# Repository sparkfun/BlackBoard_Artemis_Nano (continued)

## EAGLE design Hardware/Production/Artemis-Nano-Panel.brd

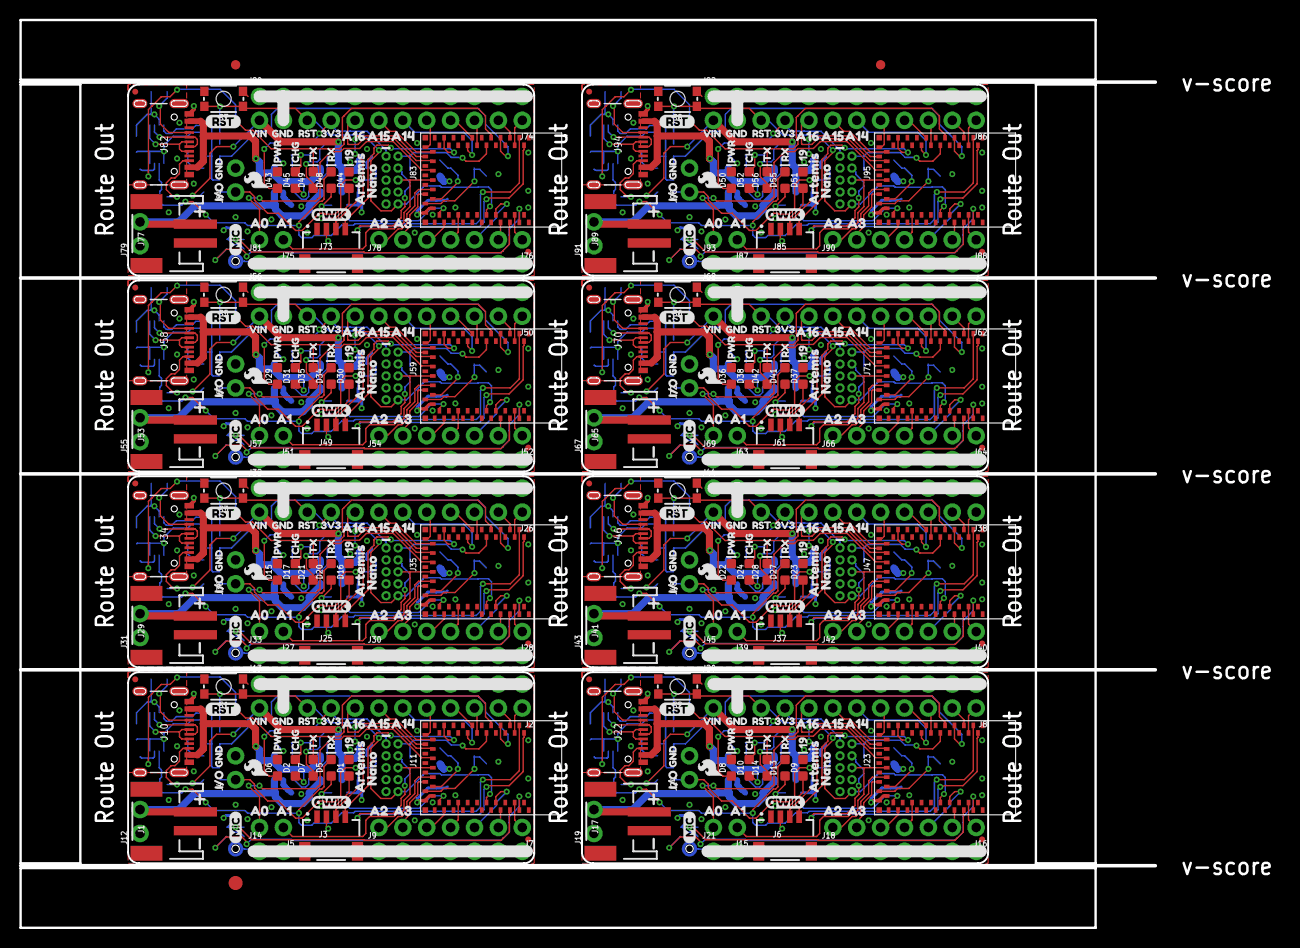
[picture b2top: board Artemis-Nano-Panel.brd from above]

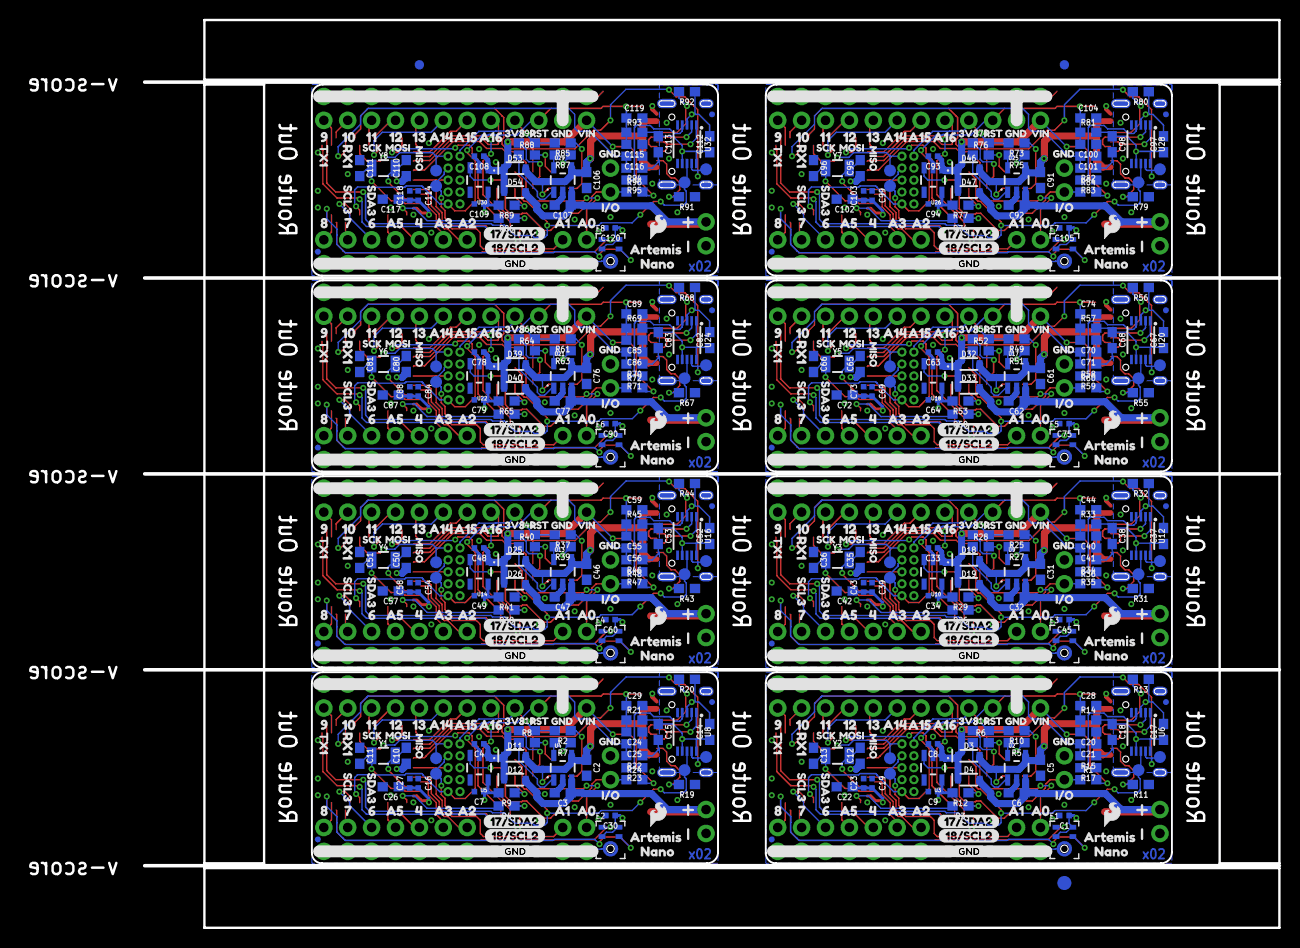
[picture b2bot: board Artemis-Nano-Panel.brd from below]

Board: 4 copper layers, 133.8 x 96.4 mm, 998 parts (627 on the bottom side), 392 nets.

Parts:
C1, C16, C19, C30, C39, C45, C54, C60, C69, C75, C84, C90, C99, C105, C114, C120: 0.1uF; 0402-TIGHT
C2, C3, C5, C6, C31, C32, C46, C47, C61, C62, C76, C77, C91, C92, C106, C107: 4.7uF; 0603
C4, C7, C8, C9, C23, C27, C33, C34, C43, C48, C49, C58, C63, C64, C73, C78, C79, C88, C93, C94, C103, C108, C109, C118: 1.0uF; 0402-TIGHT
C10, C11, C12, C13, C35, C36, C50, C51, C65, C66, C80, C81, C95, C96, C110, C111: 15pF; 0603
C14, C17, C37, C52, C67, C82, C97, C112: 10nF; 0603
C15, C18, C20, C24, C38, C40, C53, C55, C68, C70, C83, C85, C98, C100, C113, C115: 0.1uF; 0603
C21, C25, C41, C56, C71, C86, C101, C116: 2.2uF; 0603
C22, C26, C42, C57, C72, C87, C102, C117: 10uF; 0603
C28, C29, C44, C59, C74, C89, C104, C119: 1nF; 0603
D1, D9, D16, D23, D30, D37, D44, D51: BLUE; LED-0603
D2, D5, D10, D13, D17, D20, D24, D27, D31, D34, D38, D41, D45, D48, D52, D55: Yellow; LED-0603
D3, D4, D11, D12, D18, D19, D25, D26, D32, D33, D39, D40, D46, D47, D53, D54: 1A/23V/620mV; SOD-323
D6, D8, D15, D22, D29, D36, D43, D50: RED; LED-0603
D7, D14, D21, D28, D35, D42, D49, D56: GREEN; LED-0603
E1, E2, E3, E4, E5, E6, E7, E8: SPH0641LM4H; SPH0641LM4H-1_MICROPHONE
E$1, E$2, E$3, E$4: FIDUCIAL-1X2
E$5, E$6: FIDUCIAL-1.5X3
FD1, FD2, FD3, FD4, FD5, FD6, FD7, FD8, FD9, FD10, FD11, FD12, FD13, FD14, FD15, FD16, FD17, FD18, FD19, FD20, FD21, FD22, FD23, FD24, FD25, FD26, FD27, FD28, FD29, FD30, FD31, FD32: FIDUCIALUFIDUCIAL; FIDUCIAL-MICRO
FRAME1, FRAME2, FRAME3, FRAME4, FRAME5, FRAME6, FRAME7, FRAME8: FRAME-LETTERNO_PACKAGE; DUMMY
J1, J17, J29, J41, J53, J65, J77, J89: JST-2-SMD
J2, J8, J13, J20, J26, J32, J38, J44, J50, J56, J62, J68, J74, J80, J86, J92: 1X12_NO_SILK
J3, J6, J25, J37, J49, J61, J73, J85: JST04_1MM_RA
J4, J5, J12, J14, J15, J19, J21, J24, J27, J31, J33, J36, J39, J43, J45, J48, J51, J55, J57, J60, J63, J67, J69, J72, J75, J79, J81, J84, J87, J91, J93, J96: 1X02_NO_SILK
J7, J9, J16, J18, J28, J30, J40, J42, J52, J54, J64, J66, J76, J78, J88, J90: 1X07_NO_SILK
J10, J22, J34, J46, J58, J70, J82, J94: USB-C; USB-C-16P
J11, J23, J35, J47, J59, J71, J83, J95: CORTEX_DEBUG; 2X5-PTH-1.27MM-NO_SILK
LOGO1, LOGO2, LOGO3, LOGO4, LOGO5, LOGO6, LOGO7, LOGO8, LOGO9, LOGO10, LOGO11, LOGO12, LOGO13, LOGO14, LOGO15, LOGO16: SFE_LOGO_FLAME.1_INCH; SFE_LOGO_FLAME_.1
R1, R15, R22, R24, R34, R36, R46, R48, R58, R60, R70, R72, R82, R84, R94, R96: 10k; 0603
R2, R3, R4, R6, R8, R10, R25, R26, R28, R37, R38, R40, R49, R50, R52, R61, R62, R64, R73, R74, R76, R85, R86, R88: 1k; 0603
R5, R7, R27, R39, R51, R63, R75, R87: 2.0k; 0603
R9, R12, R16, R18, R29, R30, R41, R42, R53, R54, R65, R66, R77, R78, R89, R90: 4.7k; 0603
R11, R13, R19, R20, R31, R32, R43, R44, R55, R56, R67, R68, R79, R80, R91, R92: 5.1k; 0603
R14, R17, R21, R23, R33, R35, R45, R47, R57, R59, R69, R71, R81, R83, R93, R95: 100k; 0603
S1, S2, S3, S4, S5, S6, S7, S8: RESET; TACTILE_SWITCH_SMD_4.6X2.8MM
TP1, TP2, TP7, TP8, TP11, TP12, TP15, TP16, TP19, TP20, TP23, TP24, TP27, TP28, TP31, TP32: PAD.03X.05
TP3, TP4, TP5, TP6, TP9, TP10, TP13, TP14, TP17, TP18, TP21, TP22, TP25, TP26, TP29, TP30: TEST-POINT3X5; PAD.03X.05
U1, U7, U11, U15, U19, U23, U27, U31: ARTEMIS_MODULESMD; ARTEMIS_FP
U2, U4, U9, U13, U17, U21, U25, U29: MCP73831; SOT23-5
U3, U5, U10, U14, U18, U22, U26, U30: 3.3V; SOT23-5
U6, U8, U12, U16, U20, U24, U28, U32: CH340E_MSOP10; MSOP10
U$1, U$49, U$65, U$72, U$127, U$134, U$187, U$194, U$247, U$254, U$307, U$314, U$367, U$374, U$427, U$434: 3V316
U$2, U$82, U$144, U$204, U$264, U$324, U$384, U$444: ____GND____2
U$3, U$38, U$64, U$70, U$126, U$132, U$186, U$192, U$246, U$252, U$306, U$312, U$366, U$372, U$426, U$432: RST19
U$4, U$23, U$117, U$119, U$177, U$179, U$237, U$239, U$297, U$299, U$357, U$359, U$417, U$419, U$477, U$479: I#O3
U$5, U$44, U$121, U$181, U$241, U$301, U$361, U$421: CHG26
U$6, U$58, U$122, U$182, U$242, U$302, U$362, U$422: PWR27
U$7, U$29, U$33, U$43, U$62, U$69, U$118, U$120, U$124, U$131, U$178, U$180, U$184, U$191, U$238, U$240, U$244, U$251, U$298, U$300, U$304, U$311, U$358, U$360, U$364, U$371, U$418, U$420, U$424, U$431, U$478, U$480: GND17
U$8, U$61, U$123, U$183, U$243, U$303, U$363, U$423: QWIIC#LOGO#JPG
U$9, U$20, U$84, U$108, U$146, U$168, U$206, U$228, U$266, U$288, U$326, U$348, U$386, U$408, U$446, U$468: A00
U$10, U$105, U$165, U$225, U$285, U$345, U$405, U$465: A57
U$11, U$102, U$162, U$222, U$282, U$342, U$402, U$462: SCL30
U$12, U$54, U$99, U$110, U$159, U$170, U$219, U$230, U$279, U$290, U$339, U$350, U$399, U$410, U$459, U$470: A145
U$13, U$22, U$73, U$79, U$135, U$141, U$195, U$201, U$255, U$261, U$315, U$321, U$375, U$381, U$435, U$441: ARTEMIS6
U$14, U$75, U$137, U$197, U$257, U$317, U$377, U$437: MISO5
U$15, U$74, U$136, U$196, U$256, U$316, U$376, U$436: MIC0
U$16, U$76, U$138, U$198, U$258, U$318, U$378, U$438: MOSI4
U$17, U$24, U$77, U$80, U$139, U$142, U$199, U$202, U$259, U$262, U$319, U$322, U$379, U$382, U$439, U$442: NANO7
U$18, U$78, U$140, U$200, U$260, U$320, U$380, U$440: SCK3
U$19, U$42, U$93, U$106, U$153, U$166, U$213, U$226, U$273, U$286, U$333, U$346, U$393, U$406, U$453, U$466: A32
U$21, U$41, U$92, U$107, U$152, U$167, U$212, U$227, U$272, U$287, U$332, U$347, U$392, U$407, U$452, U$467: A21
U$25, U$83, U$145, U$205, U$265, U$325, U$385, U$445: PRODUCTION_INSTRUCTIONS
U$26, U$116, U$176, U$236, U$296, U$356, U$416, U$476: 191
U$27, U$39, U$63, U$71, U$125, U$133, U$185, U$193, U$245, U$253, U$305, U$313, U$365, U$373, U$425, U$433: VIN19
U$28, U$55, U$100, U$111, U$160, U$171, U$220, U$231, U$280, U$291, U$340, U$351, U$400, U$411, U$460, U$471: A156
U$30, U$81, U$143, U$203, U$263, U$323, U$383, U$443: GND2
U$31, U$103, U$163, U$223, U$283, U$343, U$403, U$463: SDA31
U$32, U$87, U$147, U$207, U$267, U$327, U$387, U$447: 46
U$34, U$40, U$91, U$109, U$151, U$169, U$211, U$229, U$271, U$289, U$331, U$349, U$391, U$409, U$451, U$469: A10
U$35, U$88, U$148, U$208, U$268, U$328, U$388, U$448: 68
U$36, U$89, U$149, U$209, U$269, U$329, U$389, U$449: 79
U$37, U$90, U$150, U$210, U$270, U$330, U$390, U$450: 810
U$45, U$94, U$154, U$214, U$274, U$334, U$394, U$454: 90
U$46, U$95, U$155, U$215, U$275, U$335, U$395, U$455: 101
U$47, U$96, U$156, U$216, U$276, U$336, U$396, U$456: 112
U$48, U$56, U$101, U$112, U$161, U$172, U$221, U$232, U$281, U$292, U$341, U$352, U$401, U$412, U$461, U$472: A167
U$50, U$113, U$173, U$233, U$293, U$353, U$413, U$473: RX10
U$51, U$66, U$128, U$188, U$248, U$308, U$368, U$428: RST1
U$52, U$97, U$157, U$217, U$277, U$337, U$397, U$457: 123
U$53, U$98, U$158, U$218, U$278, U$338, U$398, U$458: 134
U$57, U$114, U$174, U$234, U$294, U$354, U$414, U$474: 17#SDA21
U$59, U$104, U$164, U$224, U$284, U$344, U$404, U$464: TX12
U$60, U$115, U$175, U$235, U$295, U$355, U$415, U$475: 18#SCL20
U$67, U$85, U$129, U$189, U$249, U$309, U$369, U$429: RX23
U$68, U$86, U$130, U$190, U$250, U$310, U$370, U$430: TX22
Y1, Y2, Y3, Y4, Y5, Y6, Y7, Y8: 32.768kHz; CRYSTAL-SMD-3.2X1.5MM

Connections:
1: J16.1, U7.D38
2: J8.2, U7.D40
3: J28.1, U11.D38
3.3V: C1.1, C9.1, C17.1, C18.1, C19.2, C22.1, C23.1, E1.2, E1.5, J2.9, J3.2, J11.1, R10.2, R12.2, R14.2, R16.2, U1.VDD@36, U1.VDD@37, U3.5, U6.7, U6.10
3.3V1: C7.1, C14.1, C15.1, C16.2, C26.1, C27.1, C30.1, E2.2, E2.5, J6.2, J8.9, J23.1, R2.2, R9.2, R18.2, R21.2, U5.5, U7.VDD@36, U7.VDD@37, U8.7, U8.10
3.3V2: C34.1, C37.1, C38.1, C39.2, C42.1, C43.1, C45.1, E3.2, E3.5, J25.2, J26.9, J35.1, R25.2, R29.2, R30.2, R33.2, U10.5, U11.VDD@36, U11.VDD@37, U12.7, U12.10
3.3V3: C49.1, C52.1, C53.1, C54.2, C57.1, C58.1, C60.1, E4.2, E4.5, J37.2, J38.9, J47.1, R37.2, R41.2, R42.2, R45.2, U14.5, U15.VDD@36, U15.VDD@37, U16.7, U16.10
3.3V4: C64.1, C67.1, C68.1, C69.2, C72.1, C73.1, C75.1, E5.2, E5.5, J49.2, J50.9, J59.1, R49.2, R53.2, R54.2, R57.2, U18.5, U19.VDD@36, U19.VDD@37, U20.7, U20.10
3.3V5: C79.1, C82.1, C83.1, C84.2, C87.1, C88.1, C90.1, E6.2, E6.5, J61.2, J62.9, J71.1, R61.2, R65.2, R66.2, R69.2, U22.5, U23.VDD@36, U23.VDD@37, U24.7, U24.10
3.3V6: C94.1, C97.1, C98.1, C99.2, C102.1, C103.1, C105.1, E7.2, E7.5, J73.2, J74.9, J83.1, R73.2, R77.2, R78.2, R81.2, U26.5, U27.VDD@36, U27.VDD@37, U28.7, U28.10
3.3V7: C109.1, C112.1, C113.1, C114.2, C117.1, C118.1, C120.1, E8.2, E8.5, J85.2, J86.9, J95.1, R85.2, R89.2, R90.2, R93.2, U30.5, U31.VDD@36, U31.VDD@37, U32.7, U32.10
4: J26.2, U11.D40
5: J40.1, U15.D38
6: J38.2, U15.D40
7: J52.1, U19.D38
8: J7.1, U1.D38
9: J50.2, U19.D40
10: J2.2, U1.D40
11: J64.1, U23.D38
12: J62.2, U23.D40
13: J76.1, U27.D38
14: J74.2, U27.D40
15: J88.1, U31.D38
16: J86.2, U31.D40
!RESET: C20.2, C28.1, J2.10, J11.10, R14.1, S1.3, S1.4, U1.~RST
!RESET1: C24.2, C29.1, J8.10, J23.10, R21.1, S2.3, S2.4, U7.~RST
!RESET2: C40.2, C44.1, J26.10, J35.10, R33.1, S3.3, S3.4, U11.~RST
!RESET3: C55.2, C59.1, J38.10, J47.10, R45.1, S4.3, S4.4, U15.~RST
!RESET4: C70.2, C74.1, J50.10, J59.10, R57.1, S5.3, S5.4, U19.~RST
!RESET5: C85.2, C89.1, J62.10, J71.10, R69.1, S6.3, S6.4, U23.~RST
!RESET6: C100.2, C104.1, J74.10, J83.10, R81.1, S7.3, S7.4, U27.~RST
!RESET7: C115.2, C119.1, J86.10, J95.10, R93.1, S8.3, S8.4, U31.~RST
!RTS: C20.1, C21.1, R17.2, U6.4
!RTS1: C24.1, C25.1, R23.2, U8.4
!RTS2: C40.1, C41.1, R35.2, U12.4
!RTS3: C55.1, C56.1, R47.2, U16.4
!RTS4: C70.1, C71.1, R59.2, U20.4
!RTS5: C85.1, C86.1, R71.2, U24.4
!RTS6: C100.1, C101.1, R83.2, U28.4
!RTS7: C115.1, C116.1, R95.2, U32.4
BOOT: C21.2, R15.2, U1.BOOT
BOOT1: C25.2, R22.2, U7.BOOT
BOOT2: C41.2, R34.2, U11.BOOT
BOOT3: C56.2, R46.2, U15.BOOT
BOOT4: C71.2, R58.2, U19.BOOT
BOOT5: C86.2, R70.2, U23.BOOT
BOOT6: C101.2, R82.2, U27.BOOT
BOOT7: C116.2, R94.2, U31.BOOT
CC1: J10.A5, R13.2
CC2: J10.B5, R11.2
CC3: J22.B5, R19.2
CC4: J22.A5, R20.2
CC5: J34.B5, R31.2
CC6: J34.A5, R32.2
CC7: J46.B5, R43.2
CC8: J46.A5, R44.2
CC9: J58.B5, R55.2
CC10: J58.A5, R56.2
CC11: J70.B5, R67.2
CC12: J70.A5, R68.2
CC13: J82.B5, R79.2
CC14: J82.A5, R80.2
CC15: J94.B5, R91.2
CC16: J94.A5, R92.2
D+1: J10.A6, J10.B6, U6.1
D+2: J22.A6, J22.B6, U8.1
D+3: J34.A6, J34.B6, U12.1
D+4: J46.A6, J46.B6, U16.1
D+5: J58.A6, J58.B6, U20.1
D+6: J70.A6, J70.B6, U24.1
D+7: J82.A6, J82.B6, U28.1
D+8: J94.A6, J94.B6, U32.1
D-1: J10.A7, J10.B7, U6.2
D-2: J22.A7, J22.B7, U8.2
D-3: J34.A7, J34.B7, U12.2
D-4: J46.A7, J46.B7, U16.2
D-5: J58.A7, J58.B7, U20.2
D-6: J70.A7, J70.B7, U24.2
D-7: J82.A7, J82.B7, U28.2
D-8: J94.A7, J94.B7, U32.2
GND: C1.2, C5.2, C6.2, C8.2, C9.2, C12.1, C13.1, C17.2, C18.2, C19.1, C22.2, C23.2, C28.2, D1.C, D6.C, E1.3, E1.6, E1.7, E1.8, J1.1, J2.11, J3.1, J4.2, J9.1, J9.2, J9.3, J9.4, J9.5, J9.6, J9.7, J10.GND, J10.GND2, J11.3, J11.5, J11.9, J12.1, J13.1, J13.2, J13.3, J13.4, J13.5, J13.6, J13.7, J13.8, J13.9, J13.10, J13.11, J13.12, J14.1, J14.2, R5.1, R11.1, R13.1, R15.1, R17.1, S1.1, S1.2, U1.GND@1, U1.GND@22, U1.GND@38, U1.GND@39, U1.GND@47, U1.GND@59, U2.2, U3.2, U6.3
GND1: C2.2, C3.2, C4.2, C7.2, C10.1, C11.1, C14.2, C15.2, C16.1, C26.2, C27.2, C29.2, C30.2, D8.C, D9.C, E2.3, E2.6, E2.7, E2.8, J6.1, J8.11, J17.1, J18.1, J18.2, J18.3, J18.4, J18.5, J18.6, J18.7, J19.1, J20.1, J20.2, J20.3, J20.4, J20.5, J20.6, J20.7, J20.8, J20.9, J20.10, J20.11, J20.12, J21.1, J21.2, J22.GND, J22.GND2, J23.3, J23.5, J23.9, J24.2, R7.1, R19.1, R20.1, R22.1, R23.1, S2.1, S2.2, U4.2, U5.2, U7.GND@1, U7.GND@22, U7.GND@38, U7.GND@39, U7.GND@47, U7.GND@59, U8.3
GND2: C31.2, C32.2, C33.2, C34.2, C35.1, C36.1, C37.2, C38.2, C39.1, C42.2, C43.2, C44.2, C45.2, D15.C, D16.C, E3.3, E3.6, E3.7, E3.8, J25.1, J26.11, J29.1, J30.1, J30.2, J30.3, J30.4, J30.5, J30.6, J30.7, J31.1, J32.1, J32.2, J32.3, J32.4, J32.5, J32.6, J32.7, J32.8, J32.9, J32.10, J32.11, J32.12, J33.1, J33.2, J34.GND, J34.GND2, J35.3, J35.5, J35.9, J36.2, R27.1, R31.1, R32.1, R34.1, R35.1, S3.1, S3.2, U9.2, U10.2, U11.GND@1, U11.GND@22, U11.GND@38, U11.GND@39, U11.GND@47, U11.GND@59, U12.3
GND3: C46.2, C47.2, C48.2, C49.2, C50.1, C51.1, C52.2, C53.2, C54.1, C57.2, C58.2, C59.2, C60.2, D22.C, D23.C, E4.3, E4.6, E4.7, E4.8, J37.1, J38.11, J41.1, J42.1, J42.2, J42.3, J42.4, J42.5, J42.6, J42.7, J43.1, J44.1, J44.2, J44.3, J44.4, J44.5, J44.6, J44.7, J44.8, J44.9, J44.10, J44.11, J44.12, J45.1, J45.2, J46.GND, J46.GND2, J47.3, J47.5, J47.9, J48.2, R39.1, R43.1, R44.1, R46.1, R47.1, S4.1, S4.2, U13.2, U14.2, U15.GND@1, U15.GND@22, U15.GND@38, U15.GND@39, U15.GND@47, U15.GND@59, U16.3
GND4: C61.2, C62.2, C63.2, C64.2, C65.1, C66.1, C67.2, C68.2, C69.1, C72.2, C73.2, C74.2, C75.2, D29.C, D30.C, E5.3, E5.6, E5.7, E5.8, J49.1, J50.11, J53.1, J54.1, J54.2, J54.3, J54.4, J54.5, J54.6, J54.7, J55.1, J56.1, J56.2, J56.3, J56.4, J56.5, J56.6, J56.7, J56.8, J56.9, J56.10, J56.11, J56.12, J57.1, J57.2, J58.GND, J58.GND2, J59.3, J59.5, J59.9, J60.2, R51.1, R55.1, R56.1, R58.1, R59.1, S5.1, S5.2, U17.2, U18.2, U19.GND@1, U19.GND@22, U19.GND@38, U19.GND@39, U19.GND@47, U19.GND@59, U20.3
GND5: C76.2, C77.2, C78.2, C79.2, C80.1, C81.1, C82.2, C83.2, C84.1, C87.2, C88.2, C89.2, C90.2, D36.C, D37.C, E6.3, E6.6, E6.7, E6.8, J61.1, J62.11, J65.1, J66.1, J66.2, J66.3, J66.4, J66.5, J66.6, J66.7, J67.1, J68.1, J68.2, J68.3, J68.4, J68.5, J68.6, J68.7, J68.8, J68.9, J68.10, J68.11, J68.12, J69.1, J69.2, J70.GND, J70.GND2, J71.3, J71.5, J71.9, J72.2, R63.1, R67.1, R68.1, R70.1, R71.1, S6.1, S6.2, U21.2, U22.2, U23.GND@1, U23.GND@22, U23.GND@38, U23.GND@39, U23.GND@47, U23.GND@59, U24.3
GND6: C91.2, C92.2, C93.2, C94.2, C95.1, C96.1, C97.2, C98.2, C99.1, C102.2, C103.2, C104.2, C105.2, D43.C, D44.C, E7.3, E7.6, E7.7, E7.8, J73.1, J74.11, J77.1, J78.1, J78.2, J78.3, J78.4, J78.5, J78.6, J78.7, J79.1, J80.1, J80.2, J80.3, J80.4, J80.5, J80.6, J80.7, J80.8, J80.9, J80.10, J80.11, J80.12, J81.1, J81.2, J82.GND, J82.GND2, J83.3, J83.5, J83.9, J84.2, R75.1, R79.1, R80.1, R82.1, R83.1, S7.1, S7.2, U25.2, U26.2, U27.GND@1, U27.GND@22, U27.GND@38, U27.GND@39, U27.GND@47, U27.GND@59, U28.3
GND7: C106.2, C107.2, C108.2, C109.2, C110.1, C111.1, C112.2, C113.2, C114.1, C117.2, C118.2, C119.2, C120.2, D50.C, D51.C, E8.3, E8.6, E8.7, E8.8, J85.1, J86.11, J89.1, J90.1, J90.2, J90.3, J90.4, J90.5, J90.6, J90.7, J91.1, J92.1, J92.2, J92.3, J92.4, J92.5, J92.6, J92.7, J92.8, J92.9, J92.10, J92.11, J92.12, J93.1, J93.2, J94.GND, J94.GND2, J95.3, J95.5, J95.9, J96.2, R87.1, R91.1, R92.1, R94.1, R95.1, S8.1, S8.2, U29.2, U30.2, U31.GND@1, U31.GND@22, U31.GND@38, U31.GND@39, U31.GND@47, U31.GND@59, U32.3
unnamed: R5.2, U2.5
unnamed: C12.2, U1.XO, Y2.P$2
unnamed: D2.C, R6.2
unnamed: R6.1, U2.1
unnamed: D7.A, R16.1
unnamed: D8.A, R2.1
unnamed: D1.A, R3.1
unnamed: C13.2, U1.XI, Y2.P$1
unnamed: D5.A, R12.1
unnamed: D6.A, R10.1
unnamed: D9.A, R4.1
unnamed: R7.2, U4.5
unnamed: D10.C, R8.2
unnamed: R8.1, U4.1
unnamed: C10.2, U7.XO, Y1.P$2
unnamed: C11.2, U7.XI, Y1.P$1
unnamed: D14.A, R18.1
unnamed: D13.A, R9.1
unnamed: D15.A, R25.1
unnamed: D16.A, R26.1
unnamed: R27.2, U9.5
unnamed: D17.C, R28.2
unnamed: R28.1, U9.1
unnamed: C35.2, U11.XO, Y3.P$2
unnamed: C36.2, U11.XI, Y3.P$1
unnamed: D21.A, R30.1
unnamed: D20.A, R29.1
unnamed: D22.A, R37.1
unnamed: D23.A, R38.1
unnamed: R39.2, U13.5
unnamed: D24.C, R40.2
unnamed: R40.1, U13.1
unnamed: C50.2, U15.XO, Y4.P$2
unnamed: C51.2, U15.XI, Y4.P$1
unnamed: D28.A, R42.1
unnamed: D27.A, R41.1
unnamed: D29.A, R49.1
unnamed: D30.A, R50.1
unnamed: R51.2, U17.5
unnamed: D31.C, R52.2
unnamed: R52.1, U17.1
unnamed: C65.2, U19.XO, Y5.P$2
unnamed: C66.2, U19.XI, Y5.P$1
unnamed: D35.A, R54.1
unnamed: D34.A, R53.1
unnamed: D36.A, R61.1
unnamed: D37.A, R62.1
unnamed: R63.2, U21.5
unnamed: D38.C, R64.2
unnamed: R64.1, U21.1
unnamed: C80.2, U23.XO, Y6.P$2
unnamed: C81.2, U23.XI, Y6.P$1
unnamed: D42.A, R66.1
unnamed: D41.A, R65.1
unnamed: D43.A, R73.1
unnamed: D44.A, R74.1
unnamed: R75.2, U25.5
unnamed: D45.C, R76.2
unnamed: R76.1, U25.1
unnamed: C95.2, U27.XO, Y7.P$2
unnamed: C96.2, U27.XI, Y7.P$1
unnamed: D49.A, R78.1
unnamed: D48.A, R77.1
unnamed: D50.A, R85.1
unnamed: D51.A, R86.1
unnamed: R87.2, U29.5
unnamed: D52.C, R88.2
unnamed: R88.1, U29.1
unnamed: C110.2, U31.XO, Y8.P$2
unnamed: C111.2, U31.XI, Y8.P$1
unnamed: D56.A, R90.1
unnamed: D55.A, R89.1
PDMCLK: E1.4, U1.~D37
PDMCLK1: E2.4, U7.~D37
PDMCLK2: E3.4, U11.~D37
PDMCLK3: E4.4, U15.~D37
PDMCLK4: E5.4, U19.~D37
PDMCLK5: E6.4, U23.~D37
PDMCLK6: E7.4, U27.~D37
PDMCLK7: E8.4, U31.~D37
PDMDATA: E1.1, U1.D36
PDMDATA1: E2.1, U7.D36
PDMDATA2: E3.1, U11.D36
PDMDATA3: E4.1, U15.D36
PDMDATA4: E5.1, U19.D36
PDMDATA5: E6.1, U23.D36
PDMDATA6: E7.1, U27.D36
PDMDATA7: E8.1, U31.D36
RXI-0: D5.C, TP5.P$1, U1.RXI-0, U6.8
RXI-1: D13.C, TP3.P$1, U7.RXI-0, U8.8
RXI-2: D20.C, TP9.P$1, U11.RXI-0, U12.8
RXI-3: D27.C, TP13.P$1, U15.RXI-0, U16.8
RXI-4: D34.C, TP17.P$1, U19.RXI-0, U20.8
RXI-5: D41.C, TP21.P$1, U23.RXI-0, U24.8
RXI-6: D48.C, TP25.P$1, U27.RXI-0, U28.8
RXI-7: D55.C, TP29.P$1, U31.RXI-0, U32.8
SHLD: J10.SHLD1, J10.SHLD2, J10.SHLD3, J10.SHLD4, J10.SHLD5, J10.SHLD6, J10.SHLD7, J10.SHLD8
SHLD1: J22.SHLD1, J22.SHLD2, J22.SHLD3, J22.SHLD4, J22.SHLD5, J22.SHLD6, J22.SHLD7, J22.SHLD8
SHLD2: J34.SHLD1, J34.SHLD2, J34.SHLD3, J34.SHLD4, J34.SHLD5, J34.SHLD6, J34.SHLD7, J34.SHLD8
SHLD3: J46.SHLD1, J46.SHLD2, J46.SHLD3, J46.SHLD4, J46.SHLD5, J46.SHLD6, J46.SHLD7, J46.SHLD8
SHLD4: J58.SHLD1, J58.SHLD2, J58.SHLD3, J58.SHLD4, J58.SHLD5, J58.SHLD6, J58.SHLD7, J58.SHLD8
SHLD5: J70.SHLD1, J70.SHLD2, J70.SHLD3, J70.SHLD4, J70.SHLD5, J70.SHLD6, J70.SHLD7, J70.SHLD8
SHLD6: J82.SHLD1, J82.SHLD2, J82.SHLD3, J82.SHLD4, J82.SHLD5, J82.SHLD6, J82.SHLD7, J82.SHLD8
SHLD7: J94.SHLD1, J94.SHLD2, J94.SHLD3, J94.SHLD4, J94.SHLD5, J94.SHLD6, J94.SHLD7, J94.SHLD8
SWDCK: J11.4, TP1.P$1, U1.SWDCK
SWDCK1: J23.4, TP7.P$1, U7.SWDCK
SWDCK2: J35.4, TP11.P$1, U11.SWDCK
SWDCK3: J47.4, TP15.P$1, U15.SWDCK
SWDCK4: J59.4, TP19.P$1, U19.SWDCK
SWDCK5: J71.4, TP23.P$1, U23.SWDCK
SWDCK6: J83.4, TP27.P$1, U27.SWDCK
SWDCK7: J95.4, TP31.P$1, U31.SWDCK
SWDIO: J11.2, TP2.P$1, U1.SWDIO
SWDIO1: J23.2, TP8.P$1, U7.SWDIO
SWDIO2: J35.2, TP12.P$1, U11.SWDIO
SWDIO3: J47.2, TP16.P$1, U15.SWDIO
SWDIO4: J59.2, TP20.P$1, U19.SWDIO
SWDIO5: J71.2, TP24.P$1, U23.SWDIO
SWDIO6: J83.2, TP28.P$1, U27.SWDIO
SWDIO7: J95.2, TP32.P$1, U31.SWDIO
TXO-0: D7.C, TP6.P$1, U1.TXO-0, U6.9
TXO-1: D14.C, TP4.P$1, U7.TXO-0, U8.9
TXO-2: D21.C, TP10.P$1, U11.TXO-0, U12.9
TXO-3: D28.C, TP14.P$1, U15.TXO-0, U16.9
TXO-4: D35.C, TP18.P$1, U19.TXO-0, U20.9
TXO-5: D42.C, TP22.P$1, U23.TXO-0, U24.9
TXO-6: D49.C, TP26.P$1, U27.TXO-0, U28.9
TXO-7: D56.C, TP30.P$1, U31.TXO-0, U32.9
VIN: C8.1, D3.C, D4.C, J2.12, R1.2, U3.1
VIN1: C4.1, D11.C, D12.C, J8.12, R24.2, U5.1
VIN2: C33.1, D18.C, D19.C, J26.12, R36.2, U10.1
VIN3: C48.1, D25.C, D26.C, J38.12, R48.2, U14.1
VIN4: C63.1, D32.C, D33.C, J50.12, R60.2, U18.1
VIN5: C78.1, D39.C, D40.C, J62.12, R72.2, U22.1
VIN6: C93.1, D46.C, D47.C, J74.12, R84.2, U26.1
VIN7: C108.1, D53.C, D54.C, J86.12, R96.2, U30.1
VREG_EN: J4.1, R1.1, U3.3
VREG_EN1: J24.1, R24.1, U5.3
VREG_EN2: J36.1, R36.1, U10.3
VREG_EN3: J48.1, R48.1, U14.3
VREG_EN4: J60.1, R60.1, U18.3
VREG_EN5: J72.1, R72.1, U22.3
VREG_EN6: J84.1, R84.1, U26.3
VREG_EN7: J96.1, R96.1, U30.3
V_BATT: C6.1, D4.A, J1.2, J12.2, U2.3
V_BATT1: C3.1, D12.A, J17.2, J19.2, U4.3
V_BATT2: C32.1, D19.A, J29.2, J31.2, U9.3
V_BATT3: C47.1, D26.A, J41.2, J43.2, U13.3
V_BATT4: C62.1, D33.A, J53.2, J55.2, U17.3
V_BATT5: C77.1, D40.A, J65.2, J67.2, U21.3
V_BATT6: C92.1, D47.A, J77.2, J79.2, U25.3
V_BATT7: C107.1, D54.A, J89.2, J91.2, U29.3
V_USB: C5.1, D2.A, D3.A, J10.VBUS1, J10.VBUS2, U2.4
V_USB1: C2.1, D10.A, D11.A, J22.VBUS1, J22.VBUS2, U4.4
V_USB2: C31.1, D17.A, D18.A, J34.VBUS1, J34.VBUS2, U9.4
V_USB3: C46.1, D24.A, D25.A, J46.VBUS1, J46.VBUS2, U13.4
V_USB4: C61.1, D31.A, D32.A, J58.VBUS1, J58.VBUS2, U17.4
V_USB5: C76.1, D38.A, D39.A, J70.VBUS1, J70.VBUS2, U21.4
V_USB6: C91.1, D45.A, D46.A, J82.VBUS1, J82.VBUS2, U25.4
V_USB7: C106.1, D52.A, D53.A, J94.VBUS1, J94.VBUS2, U29.4
~1: J8.4, U7.D7
~2: J8.5, U7.~D6
~3: J8.3, U7.~D5
~4: J7.5, U1.~D18
~5: J16.2, U7.~D42
~6: J7.3, U1.~D43
~7: J7.2, U1.~D42
~8: J16.3, U7.~D43
~9: J2.1, U1.~D39
~10: J8.1, U7.~D39
~11: J2.3, U1.~D5
~12: J2.4, U1.D7
~13: J2.5, U1.~D6
~14: J16.5, U7.~D18
~15: J26.4, U11.D7
~16: J26.5, U11.~D6
~17: J26.3, U11.~D5
~18: J28.2, U11.~D42
~19: J28.3, U11.~D43
~20: J26.1, U11.~D39
~21: J28.5, U11.~D18
~22: J38.4, U15.D7
~23: J38.5, U15.~D6
~24: J38.3, U15.~D5
~25: J40.2, U15.~D42
~26: J40.3, U15.~D43
~27: J38.1, U15.~D39
~28: J40.5, U15.~D18
~29: J50.4, U19.D7
~30: J50.5, U19.~D6
~31: J50.3, U19.~D5
~32: J52.2, U19.~D42
~33: J52.3, U19.~D43
~34: J50.1, U19.~D39
~35: J52.5, U19.~D18
~36: J62.4, U23.D7
~37: J62.5, U23.~D6
~38: J62.3, U23.~D5
~39: J64.2, U23.~D42
~40: J64.3, U23.~D43
~41: J62.1, U23.~D39
~42: J64.5, U23.~D18
~43: J74.4, U27.D7
~44: J74.5, U27.~D6
~45: J74.3, U27.~D5
~46: J76.2, U27.~D42
~47: J76.3, U27.~D43
~48: J74.1, U27.~D39
~49: J76.5, U27.~D18
~50: J86.4, U31.D7
~51: J86.5, U31.~D6
~52: J86.3, U31.~D5
~53: J88.2, U31.~D42
~54: J88.3, U31.~D43
~55: J86.1, U31.~D39
~56: J88.5, U31.~D18
~A0: J5.2, U1.~AD13
~A1: J5.1, J11.6, U1.~AD33/SWO
~A2: J7.7, U1.~AD11
~A3: J7.6, U1.~AD29
~A4: J15.1, J23.6, U7.~AD33/SWO
~A5: J7.4, U1.~AD31
~A6: J16.6, U7.~AD29
~A7: J16.7, U7.~AD11
~A8: J8.6, U7.~AD35
~A9: J8.7, U7.~AD32
~A10: J8.8, U7.~AD12
~A11: J15.2, U7.~AD13
~A12: J16.4, U7.~AD31
~A13: J27.1, J35.6, U11.~AD33/SWO
~A14: J2.6, U1.~AD35
~A15: J2.7, U1.~AD32
~A16: J2.8, U1.~AD12
~A17: J28.6, U11.~AD29
~A18: J28.7, U11.~AD11
~A19: J26.6, U11.~AD35
~A20: J26.7, U11.~AD32
~A21: J26.8, U11.~AD12
~A22: J27.2, U11.~AD13
~A23: J28.4, U11.~AD31
~A24: J39.1, J47.6, U15.~AD33/SWO
~A25: J40.6, U15.~AD29
~A26: J40.7, U15.~AD11
~A27: J38.6, U15.~AD35
~A28: J38.7, U15.~AD32
~A29: J38.8, U15.~AD12
~A30: J39.2, U15.~AD13
~A31: J40.4, U15.~AD31
~A32: J51.1, J59.6, U19.~AD33/SWO
~A33: J52.6, U19.~AD29
~A34: J52.7, U19.~AD11
~A35: J50.6, U19.~AD35
~A36: J50.7, U19.~AD32
~A37: J50.8, U19.~AD12
~A38: J51.2, U19.~AD13
~A39: J52.4, U19.~AD31
~A40: J63.1, J71.6, U23.~AD33/SWO
~A41: J64.6, U23.~AD29
~A42: J64.7, U23.~AD11
~A43: J62.6, U23.~AD35
~A44: J62.7, U23.~AD32
~A45: J62.8, U23.~AD12
~A46: J63.2, U23.~AD13
~A47: J64.4, U23.~AD31
~A48: J75.1, J83.6, U27.~AD33/SWO
~A49: J76.6, U27.~AD29
~A50: J76.7, U27.~AD11
~A51: J74.6, U27.~AD35
~A52: J74.7, U27.~AD32
~A53: J74.8, U27.~AD12
~A54: J75.2, U27.~AD13
~A55: J76.4, U27.~AD31
~A56: J87.1, J95.6, U31.~AD33/SWO
~A57: J88.6, U31.~AD29
~A58: J88.7, U31.~AD11
~A59: J86.6, U31.~AD35
~A60: J86.7, U31.~AD32
~A61: J86.8, U31.~AD12
~A62: J87.2, U31.~AD13
~A63: J88.4, U31.~AD31
~D19/LED: R3.2, U1.~D19
~D19/LED1: R4.2, U7.~D19
~D19/LED2: R26.2, U11.~D19
~D19/LED3: R38.2, U15.~D19
~D19/LED4: R50.2, U19.~D19
~D19/LED5: R62.2, U23.~D19
~D19/LED6: R74.2, U27.~D19
~D19/LED7: R86.2, U31.~D19
~D25/SDA1: J6.3, U7.~D25
~D25/SDA2: J3.3, U1.~D25
~D25/SDA3: J25.3, U11.~D25
~D25/SDA4: J37.3, U15.~D25
~D25/SDA5: J49.3, U19.~D25
~D25/SDA6: J61.3, U23.~D25
~D25/SDA7: J73.3, U27.~D25
~D25/SDA8: J85.3, U31.~D25
~D27/SCL1: J6.4, U7.~D27
~D27/SCL2: J3.4, U1.~D27
~D27/SCL3: J25.4, U11.~D27
~D27/SCL4: J37.4, U15.~D27
~D27/SCL5: J49.4, U19.~D27
~D27/SCL6: J61.4, U23.~D27
~D27/SCL7: J73.4, U27.~D27
~D27/SCL8: J85.4, U31.~D27

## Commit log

2019-05-15 Rename to Nano. Add ignore. Add panel.
2019-05-20 Fixing PWM pin 7. Updating schematic symbol.
2019-05-22 Fix pin 33 silk
2019-06-05 Change silk to match new variant
2019-06-05 Fixed TX/RX LED label swap
2019-06-20 Changing bootload circuit to match what is being shipped. Add ignore.
2019-06-20 Readme update
2019-06-21 Adding charge rate to sch
2019-06-24 Update README.md
    Update documentation links
2019-06-24 Modify BL reset circuit to work with POR, SBL, and SVL
    RTS doesn't like a 10k pull down. Remove R17. Increased R15 to 220k and reduced C21 to 0.1uF to maintain same RC time constant. Works for POR, SBL, and SVL.
